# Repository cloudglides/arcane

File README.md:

<h1 align="center">
  <br>
  
  <br>
  Ara
  <br>
</h1>
<h4 align="center">
Open Time. Open Source.
</h4>
<div align="center">

</div>
<p align="center">
  <a href="#key-features">Key Features</a> •
  <a href="#pcb">PCB</a> •
  <a href="#credits">Credits</a> 
</p>

<p>&nbsp;</p>

Ara is a custom watch PCB built around STM32, and LiPo charging into a 2 layer manufacturable board.
Built because most smartwatches don't let you know whats inside. Ara is designed from scratch open source and exactly what's needed.

To build your own, grab the KiCad files, review the schematic below, and send the panelized design to your preferred PCB fab. Flash your firmware over STM32 HEADER PINS and you're good to go.

Every smartwatch on the market is firmware locked. Ara exists to change that.

## Key Features
- **STM32** microcontroller which can go into ultra low power mode
- **Battery charging** with Integrated IC and solder pad for 1S LiPo
- **Multiple Status LEDs** for visual feedback
- **USB-C** connectivity
- **Panelized design** for cost-effective manufacturing

## PCB

Designed in KiCad with attention to power management, and IC integration. The board features a 2-layer optimized routing.

### Schematic

---

### PCB Layers

#### Layer 1

#### Layer 2

---

### Board Views

#### Front

#### Back

### Zine

## Credits

This project uses:
- [KiCad](https://www.kicad.org/)
- [Blender](https://www.blender.org/) for renders
- [Hack Club Fallout](https://fallout.hackclub.com)

## License

GPL

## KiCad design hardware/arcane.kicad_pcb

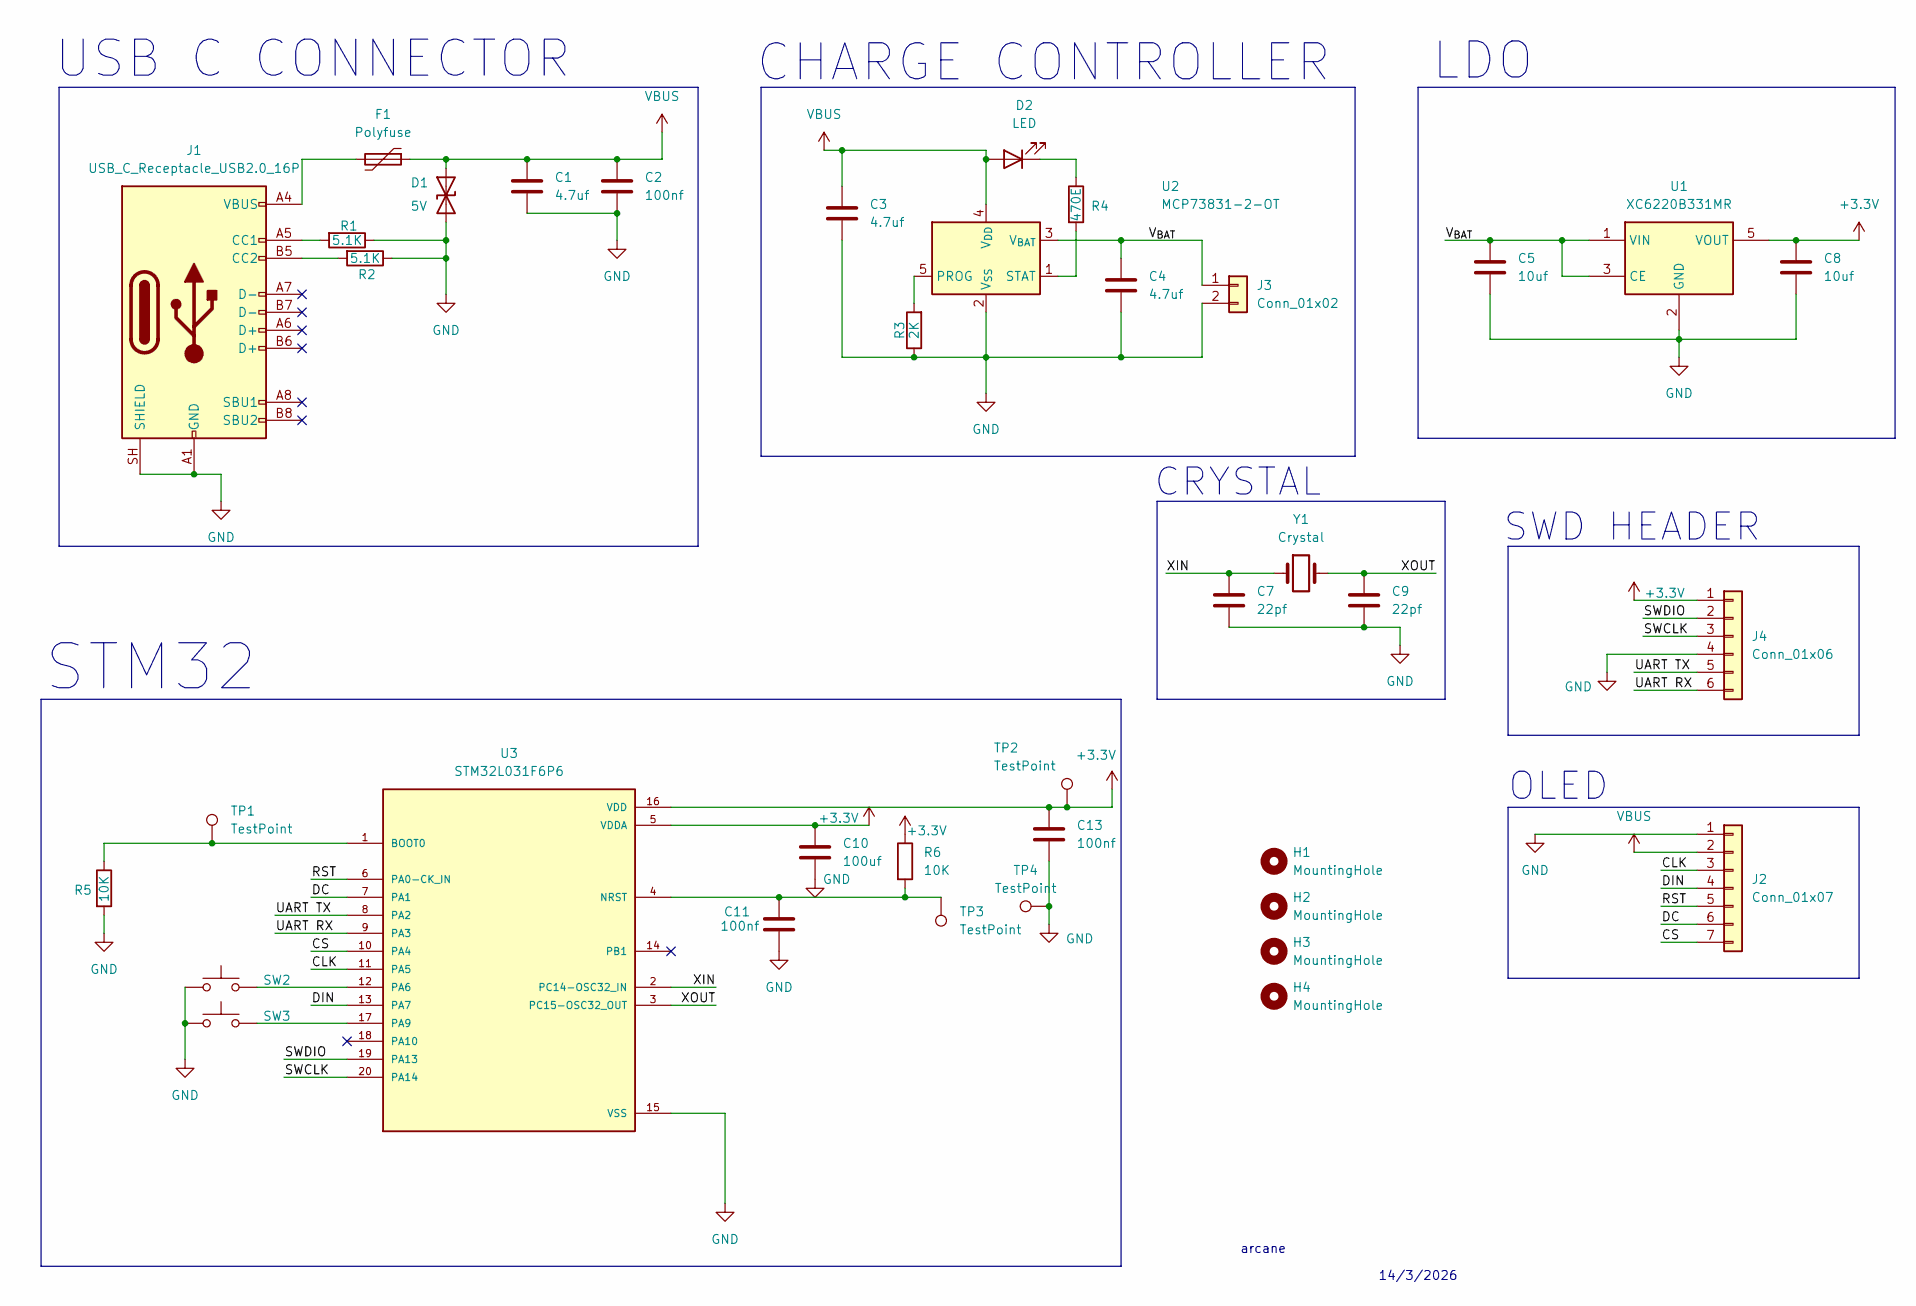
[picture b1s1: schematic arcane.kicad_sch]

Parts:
C1, C3, C4: 4.7uf; C_0603_1608Metric_Pad1.08x0.95mm_HandSolder
C2, C11, C13: 100nf; C_0603_1608Metric_Pad1.08x0.95mm_HandSolder
C5, C8: 10uf; C_0603_1608Metric_Pad1.08x0.95mm_HandSolder
C7, C9: 22pf; C_0402_1005Metric_Pad0.74x0.62mm_HandSolder
C10: 100uf; C_0603_1608Metric_Pad1.08x0.95mm_HandSolder
D1: 5V; D_SOD-123; LCSC Part C82044
D2: LED; LED_0402_1005Metric_Pad0.77x0.64mm_HandSolder
F1: Polyfuse; Fuse_0805_2012Metric_Pad1.15x1.40mm_HandSolder
H1, H2, H3, H4: MountingHole; MountingHole_2.2mm_M2
J1: USB_C_Receptacle_USB2.0_16P; USB_C_Receptacle_HRO_TYPE-C-31-M-12
J2: Conn_01x07; PinHeader_1x07_P2.54mm_Vertical
J3: Conn_01x02; JST_XH_S2B-XH-A_1x02_P2.50mm_Horizontal
J4: Conn_01x06; PinHeader_1x06_P2.54mm_Vertical
R1, R2: 5.1K; R_0603_1608Metric_Pad0.98x0.95mm_HandSolder
R3: 2K; R_0603_1608Metric_Pad0.98x0.95mm_HandSolder
R4: 470E; R_0603_1608Metric_Pad0.98x0.95mm_HandSolder
R5, R6: 10K; R_0603_1608Metric_Pad0.98x0.95mm_HandSolder
SW2, SW3: SW_Push; SW_SPST_TL3342
TP1, TP2, TP3, TP4: TestPoint; TestPoint_Pad_1.0x1.0mm
U1: XC6220B331MR; SOT-23-5
U2: MCP73831-2-OT; SOT-23-5
U3: STM32L031F6P6; SOP65P640X120-20N; PARTREV 6
Y1: Crystal; Crystal_SMD_3215-2Pin_3.2x1.5mm

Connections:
+3.3V: C8.1, C10.1, C13.1, J4.1, R6.1, TP2.1 (1_1), U1.5 (VOUT), U3.5 (VDDA), U3.16 (VDD)
/CLK: J2.3, U3.11 (PA5)
/CS: J2.7, U3.10 (PA4)
/DC: J2.6, U3.7 (PA1)
/DIN: J2.4, U3.13 (PA7)
/RST: J2.5, U3.6 (PA0-CK_IN)
/SWCLK: J4.3, U3.20 (PA14)
/SWDIO: J4.2, U3.19 (PA13)
/UART RX: J4.6, U3.9 (PA3)
/UART TX: J4.5, U3.8 (PA2)
/V_{BAT}: C4.1, C5.1, J3.1, U1.1 (VIN), U1.3 (CE), U2.3 (V_{BAT})
/XIN: C7.1, U3.2 (PC14-OSC32_IN), Y1.1
/XOUT: C9.1, U3.3 (PC15-OSC32_OUT), Y1.2
GND: C1.2, C2.2, C3.2, C4.2, C5.2, C7.2, C8.2, C9.2, C10.2, C11.2, C13.2, D1.2 (A2), J1.A1 (GND), J1.A12 (GND), J1.B1 (GND), J1.B12 (GND), J1.SH (SHIELD), J2.1, J3.2, J4.4, R1.1, R2.1, R3.1, R5.2, SW2.1, SW3.1, TP4.1 (1_1), U1.2 (GND), U2.2 (V_{SS}), U3.15 (VSS)
unnamed: D2.1 (K), R4.1
unnamed: F1.2, J1.A4 (VBUS), J1.A9 (VBUS), J1.B4 (VBUS), J1.B9 (VBUS)
unnamed: J1.A5 (CC1), R1.2
unnamed: J1.B5 (CC2), R2.2
unnamed: R3.2, U2.5 (PROG)
unnamed: R4.2, U2.1 (STAT)
unnamed: R5.1, TP1.1 (1_1), U3.1 (BOOT0)
unnamed: C11.1, R6.2, TP3.1 (1_1), U3.4 (NRST)
unnamed: SW2.2, U3.12 (PA6)
unnamed: SW3.2, U3.17 (PA9)
VBUS: C1.1, C2.1, C3.1, D1.1 (A1), D2.2 (A), F1.1, J2.2, U2.4 (V_{DD})

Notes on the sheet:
OLED
CRYSTAL
14/3/2026
SWD HEADER
arcane
CHARGE CONTROLLER
LDO
USB C CONNECTOR
STM32

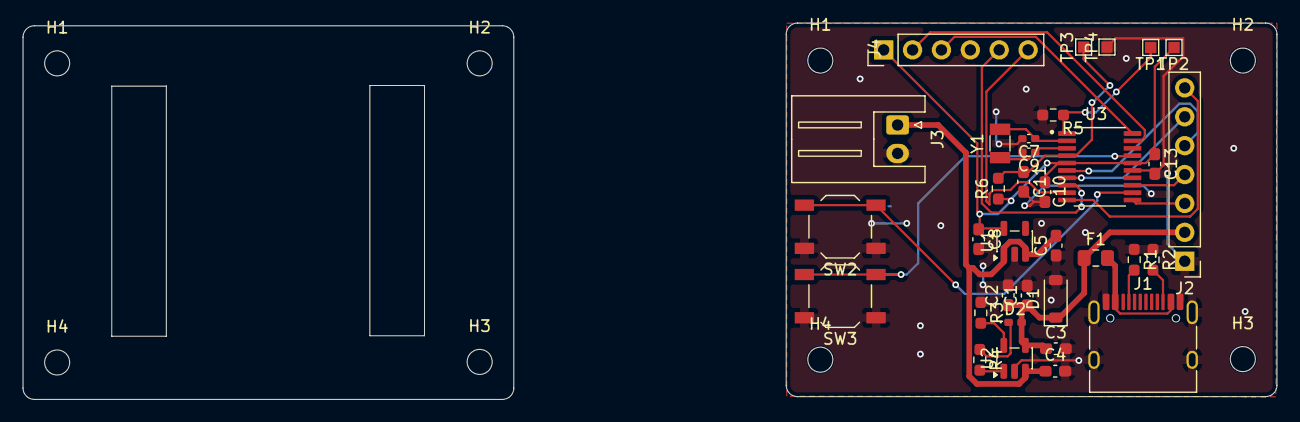
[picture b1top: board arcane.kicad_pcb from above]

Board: 2 copper layers, 110.2 x 33.1 mm, 42 parts (0 on the bottom side), 25 nets.

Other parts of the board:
H1#2, H2#2, H3#2, H4#2: MountingHole; MountingHole_2.2mm_M2

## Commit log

2026-04-06 inital commit
2026-04-06 update: add readme
2026-04-07 add: firmware and prod files
2026-04-07 update: panelize PCB for prod
2026-04-07 add: gerber files
2026-04-07 update: zine & bom
2026-04-07 [ImgBot] Optimize images
    *Total -- 3,786.73kb -> 2,962.22kb (21.77%)
    /onshape/sketch.png -- 43.68kb -> 14.41kb (67.02%)
    /zine/zine.png -- 2,249.94kb -> 1,616.02kb (28.17%)
    /onshape/translucent.png -- 40.88kb -> 32.52kb (20.45%)
    /assets/public/assembled.png -- 352.00kb -> 286.31kb (18.66%)
    /onshape/assembled.png -- 73.68kb -> 61.27kb (16.85%)
2026-04-07 update: zine in readme
2026-04-07 update: onshape timeline link
2026-04-08 update: BOM && firmware
2026-04-08 update: readme
2026-04-08 fix: BOM source
2026-04-24 Update BOM.csv
    Reorganized BOM.csv by updating header and adding items.
2026-05-04 migrate to stm32
2026-05-05 update: zine
2026-05-11 update: zine, firmware and gerber
2026-05-11 [ImgBot] Optimize images
    *Total -- 5,021.70kb -> 3,798.59kb (24.36%)
    /blender/render.png -- 2,075.71kb -> 1,426.81kb (31.26%)
    /assets/ara.png -- 1,594.98kb -> 1,173.51kb (26.42%)
    /assets/render-removebg-preview.png -- 199.21kb -> 167.69kb (15.82%)
    /hardware/Production/arcane_panelized.png -- 429.99kb -> 379.27kb (11.8%)
    /production/arcane_panelized.png -- 429.99kb -> 379.27kb (11.8%)
